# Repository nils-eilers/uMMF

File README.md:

µMMF
====

The SuperPET is basically a Commodore CBM 8032 with two, later only one
extra boards in it which contain a 6809 CPU, 64 KB RAM and some ROMs. This
project aims to provide a replacement for these extra board(s) with
slightly more modern parts, enabling every CBM 8032 owner to upgrade his
machine to a SuperPET.

__This board requires a NMOS 6502. Do NOT use a CMOS 6502!__

The board will accept NMOS Motorola 6809E as well as CMOS Hitachi HD63C09E,
just ensure you get the E-type, not those without appended ‘E’ because
their pinout is different. The version without E has the clock generator
integrated, the E-version requires an external clock generator.

LED D1 is a low current (2 mA) type. It is used solely for debug purposes,
the original SuperPET does not contain such a LED, so you may omit it.

IC3 74HCT11 has to be a HCT type. Do not use HC, LS or anything else
because HCT was chosen to match the voltage level requirements.

Please note that some modifications on the original CBM 8032 motherboard
must been made, as on the original SuperPET boards:

- 16 MHz clock signal provided at pin 35 of the 6502 CPU socket (patched in
  with a wire)
- 2532 character EPROM replacement

Refer to the pictures provided in the doc subdirectory for information
about how to provide the 16 MHz clock signal at pin 35. These differ
slightly from board version to board version.

An Atmel AT29C010 Flash ROM is required, programmed with roms/superpet.bin
and write protected.

The CPLD code was written in Verilog. These were my first steps with
Verilog, so please bear with me. Use Altera Quartus II 13.0.1 SP1 to
compile the Verilog and program the CPLD, newer versions don't support
the MAX7000 CPLD series any longer. The binary to program the CPLD is
located at cpld/output_files/superpet.pof.

An interactive bill of materials is available at `bom/ibom.html`

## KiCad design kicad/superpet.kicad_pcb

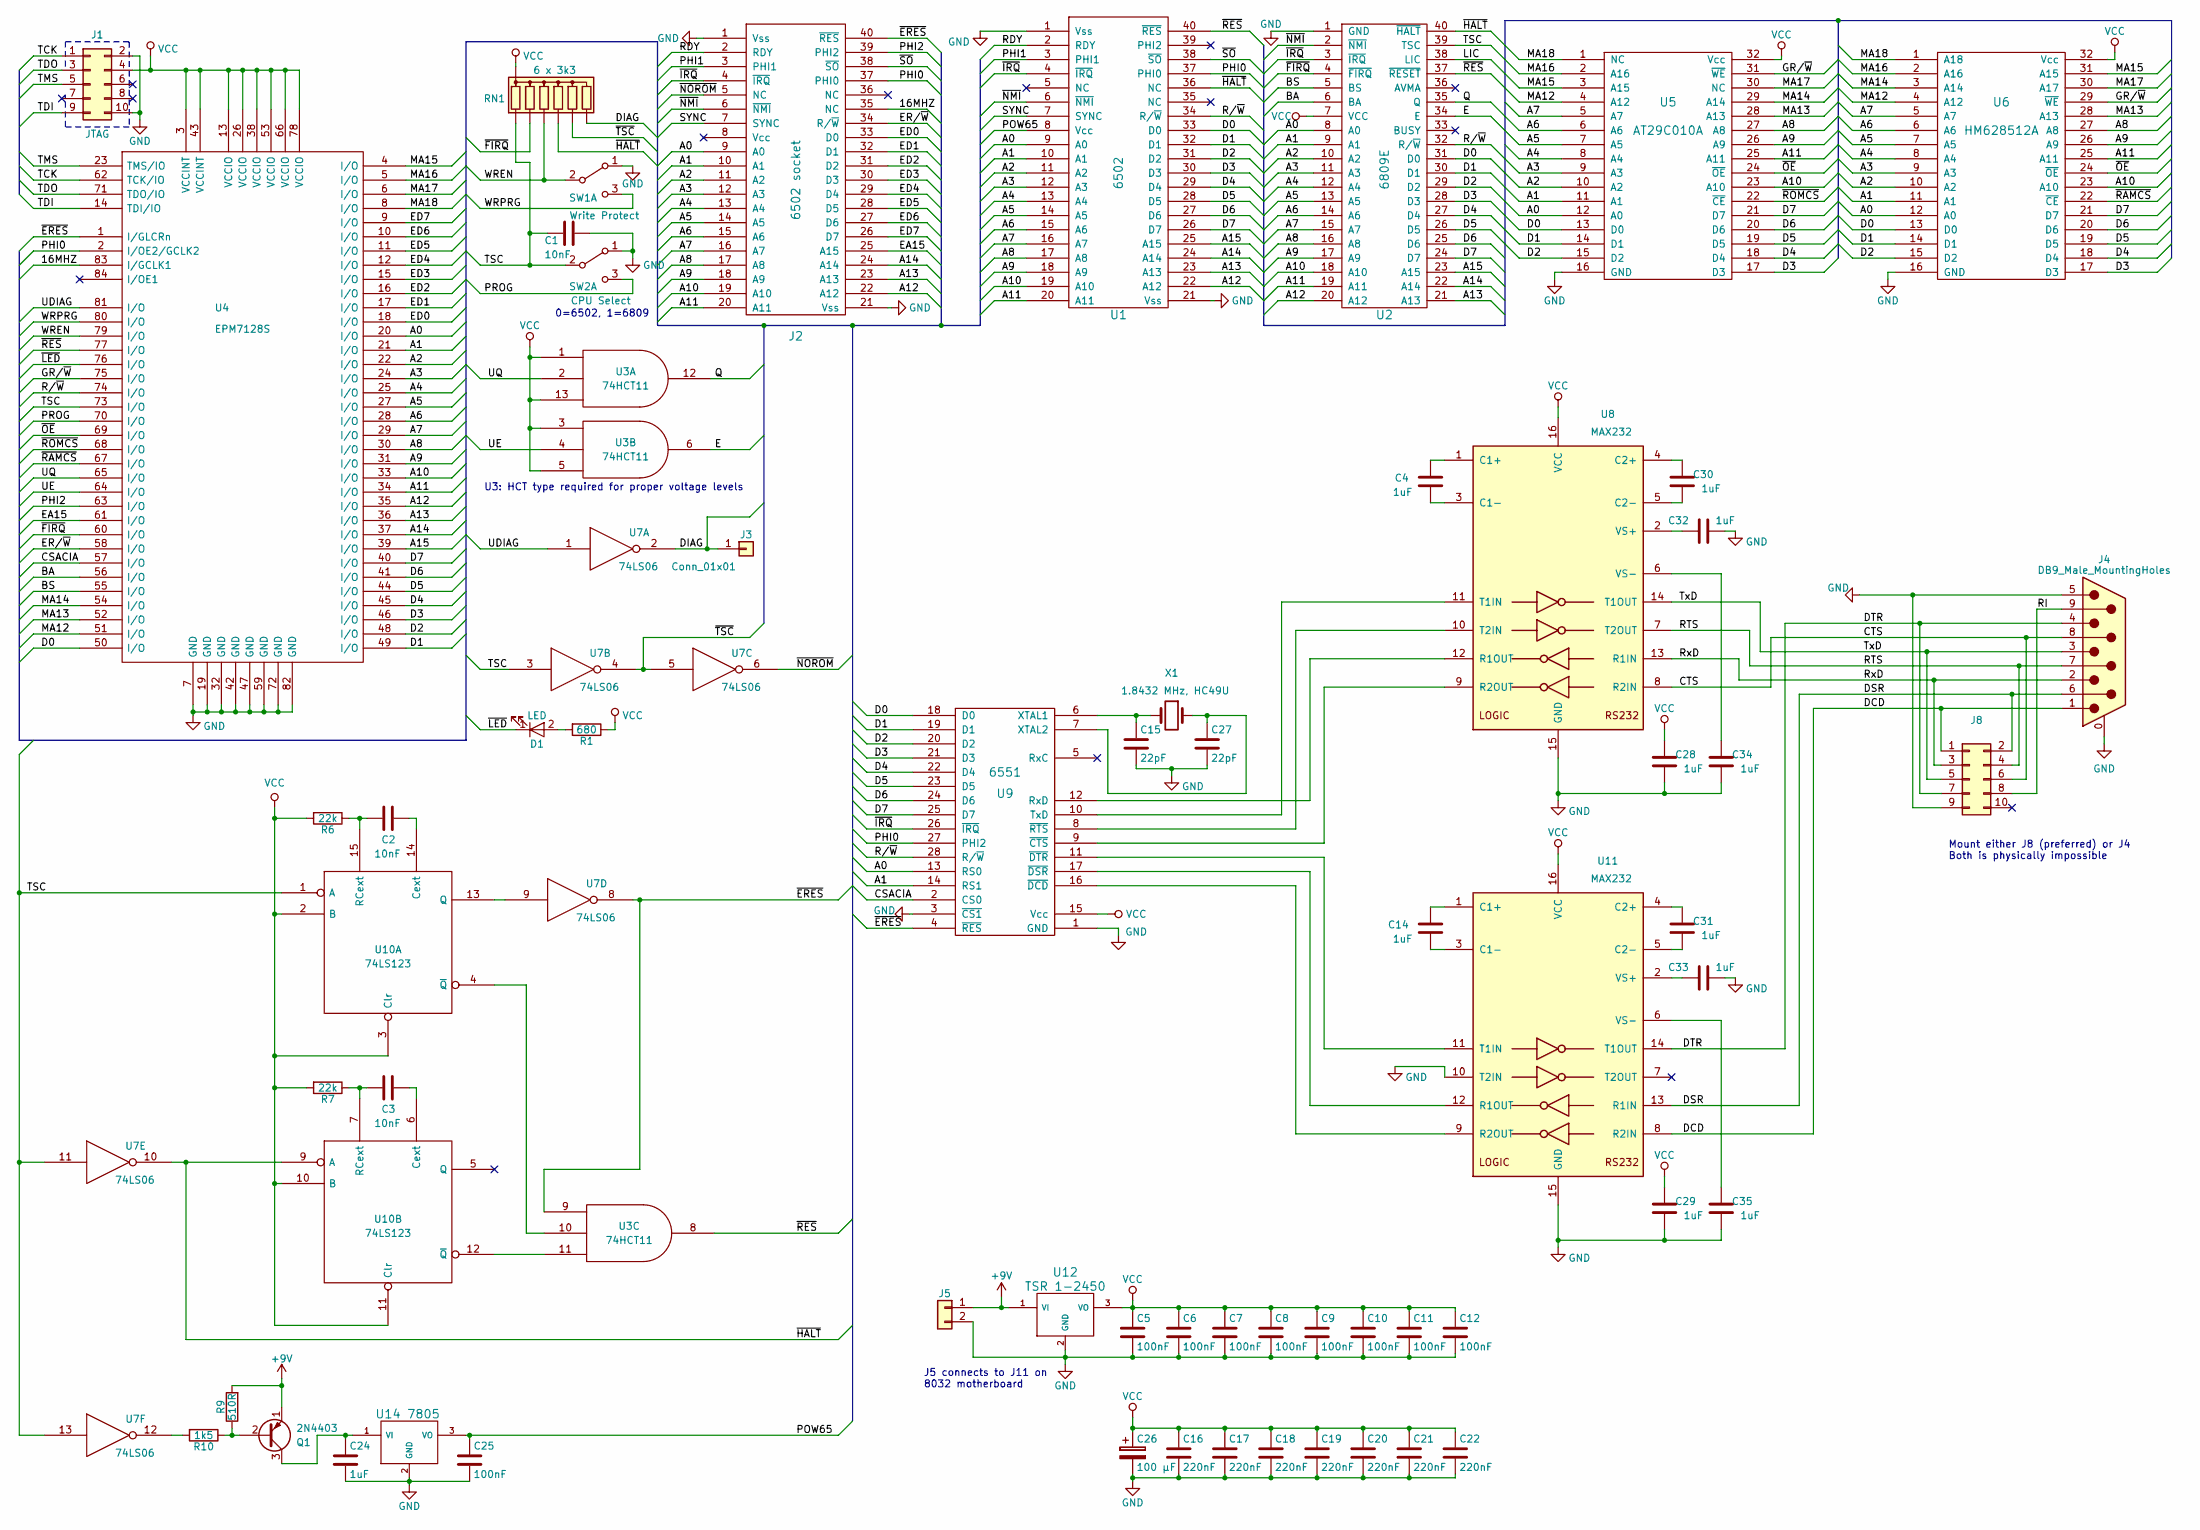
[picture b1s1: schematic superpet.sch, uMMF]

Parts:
C1, C2, C3: 10nF; C_Disc_D5.0mm_W2.5mm_P5.00mm
C4, C14, C24, C28, C29, C30, C31, C32, C33, C34, C35: 1uF; C_Disc_D5.0mm_W2.5mm_P5.00mm
C5, C6, C7, C8, C9, C10, C11, C12, C25: 100nF; C_Disc_D5.0mm_W2.5mm_P5.00mm
C15, C27: 22pF; C_Disc_D5.0mm_W2.5mm_P2.50mm
C16, C17, C18, C19, C20, C21, C22: 220nF; C_Disc_D5.0mm_W2.5mm_P5.00mm
C26: 100 µF; CP_Radial_D6.3mm_P2.50mm
D1: LED; LED_D3.0mm
J1: JTAG; Multicomp_MC9A12-1034_2x05x2.54mm_Straight
J2: 6502 socket; DIP-40_W15.24mm
J3: Conn_01x01; SolderWirePad_single_1mmDrill
J4: DB9_Male_MountingHoles; DB9MC
J5: Conn_01x02; Molex_KK-6410-02_02x2.54mm_Straight
J8: Conn_02x05_Odd_Even; Multicomp_MC9A12-1034_2x05x2.54mm_Straight
Q1: 2N4403; TO-92
R1: 680; R_Axial_DIN0207_L6.3mm_D2.5mm_P7.62mm_Horizontal
R6, R7: 22k; R_Axial_DIN0207_L6.3mm_D2.5mm_P7.62mm_Horizontal
R9: 510R; R_Axial_DIN0207_L6.3mm_D2.5mm_P7.62mm_Horizontal
R10: 1k5; R_Axial_DIN0207_L6.3mm_D2.5mm_P7.62mm_Horizontal
RN1: 6 x 3k3; R_Array_SIP7
SW1: Write Protect; WSL_6W_HALF
SW2: CPU Select; WSL_6W_HALF
U1: 6502; DIP-40_W15.24mm
U2: 6809E; DIP-40_W15.24mm
U3: 74HCT11; DIP-14_W7.62mm
U4: EPM7128S; PLCC-84_THT-Socket
U5: AT29C010A; DIP-32-15.24
U6: HM628512A; DIP-32-15.24
U7: 74LS06; DIP-14_W7.62mm
U8, U11: MAX232; DIP-16_W7.62mm
U9: 6551; DIP-28
U10: 74LS123; DIP-16_W7.62mm
U12: TSR 1-2450; TO-220-3_Vertical
U14: 7805; TO-220-3_Vertical
X1: 1.8432 MHz, HC49U; Crystal_HC49-U_Vertical

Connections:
+9V: J5.1, Q1.1 (E), R9.2, U12.1 (VI)
/16MHZ: J2.35 (NC), U4.83 (I/GCLK1)
/A0: J2.9 (A0), U1.9 (A0), U2.8 (A0), U4.20 (I/O), U5.12 (A0), U6.12 (A0), U9.13 (RS0)
/A1: J2.10 (A1), U1.10 (A1), U2.9 (A1), U4.21 (I/O), U5.11 (A1), U6.11 (A1), U9.14 (RS1)
/A2: J2.11 (A2), U1.11 (A2), U2.10 (A2), U4.22 (I/O), U5.10 (A2), U6.10 (A2)
/A3: J2.12 (A3), U1.12 (A3), U2.11 (A3), U4.24 (I/O), U5.9 (A3), U6.9 (A3)
/A4: J2.13 (A4), U1.13 (A4), U2.12 (A4), U4.25 (I/O), U5.8 (A4), U6.8 (A4)
/A5: J2.14 (A5), U1.14 (A5), U2.13 (A5), U4.27 (I/O), U5.7 (A5), U6.7 (A5)
/A6: J2.15 (A6), U1.15 (A6), U2.14 (A6), U4.28 (I/O), U5.6 (A6), U6.6 (A6)
/A7: J2.16 (A7), U1.16 (A7), U2.15 (A7), U4.29 (I/O), U5.5 (A7), U6.5 (A7)
/A8: J2.17 (A8), U1.17 (A8), U2.16 (A8), U4.30 (I/O), U5.27 (A8), U6.27 (A8)
/A9: J2.18 (A9), U1.18 (A9), U2.17 (A9), U4.31 (I/O), U5.26 (A9), U6.26 (A9)
/A10: J2.19 (A10), U1.19 (A10), U2.18 (A10), U4.33 (I/O), U5.23 (A10), U6.23 (A10)
/A11: J2.20 (A11), U1.20 (A11), U2.19 (A11), U4.34 (I/O), U5.25 (A11), U6.25 (A11)
/A12: J2.22 (A12), U1.22 (A12), U2.20 (A12), U4.35 (I/O)
/A13: J2.23 (A13), U1.23 (A13), U2.21 (A13), U4.36 (I/O)
/A14: J2.24 (A14), U1.24 (A14), U2.22 (A14), U4.37 (I/O)
/A15: U1.25 (A15), U2.23 (A15), U4.39 (I/O)
/BA: U2.6 (BA), U4.56 (I/O)
/BS: U2.5 (BS), U4.55 (I/O)
/CSACIA: U4.57 (I/O), U9.2 (CS0)
/CTS: J4.8, J8.6, U8.8 (R2IN)
/D0: U1.33 (D0), U2.31 (D0), U4.50 (I/O), U5.13 (D0), U6.13 (D0), U9.18 (D0)
/D1: U1.32 (D1), U2.30 (D1), U4.49 (I/O), U5.14 (D1), U6.14 (D1), U9.19 (D1)
/D2: U1.31 (D2), U2.29 (D2), U4.48 (I/O), U5.15 (D2), U6.15 (D2), U9.20 (D2)
/D3: U1.30 (D3), U2.28 (D3), U4.46 (I/O), U5.17 (D3), U6.17 (D3), U9.21 (D3)
/D4: U1.29 (D4), U2.27 (D4), U4.45 (I/O), U5.18 (D4), U6.18 (D4), U9.22 (D4)
/D5: U1.28 (D5), U2.26 (D5), U4.44 (I/O), U5.19 (D5), U6.19 (D5), U9.23 (D5)
/D6: U1.27 (D6), U2.25 (D6), U4.41 (I/O), U5.20 (D6), U6.20 (D6), U9.24 (D6)
/D7: U1.26 (D7), U2.24 (D7), U4.40 (I/O), U5.21 (D7), U6.21 (D7), U9.25 (D7)
/DCD: J4.1, J8.1, U11.8 (R2IN)
/DIAG: J3.1, RN1.7 (R6), U7.2
/DSR: J4.6, J8.2, U11.13 (R1IN)
/DTR: J4.4, J8.7, U11.14 (T1OUT)
/E: U2.34 (E), U3.6
/EA15: J2.25 (A15), U4.61 (I/O)
/ED0: J2.33 (D0), U4.18 (I/O)
/ED1: J2.32 (D1), U4.17 (I/O)
/ED2: J2.31 (D2), U4.16 (I/O)
/ED3: J2.30 (D3), U4.15 (I/O)
/ED4: J2.29 (D4), U4.12 (I/O)
/ED5: J2.28 (D5), U4.11 (I/O)
/ED6: J2.27 (D6), U4.10 (I/O)
/ED7: J2.26 (D7), U4.9 (I/O)
/ER/~W: J2.34 (R/~W), U4.58 (I/O)
/GR/~W: U4.75 (I/O), U5.31 (~WE), U6.29 (~WE)
/LIC: U2.38 (LIC)
/MA12: U4.51 (I/O), U5.4 (A12), U6.4 (A12)
/MA13: U4.52 (I/O), U5.28 (A13), U6.28 (A13)
/MA14: U4.54 (I/O), U5.29 (A14), U6.3 (A14)
/MA15: U4.4 (I/O), U5.3 (A15), U6.31 (A15)
/MA16: U4.5 (I/O), U5.2 (A16), U6.2 (A16)
/MA17: U4.6 (I/O), U5.30 (NC), U6.30 (A17)
/MA18: U4.8 (I/O), U5.1 (NC), U6.1 (A18)
/PHI0: J2.37 (PHI0), U1.37 (PHI0), U4.2 (I/OE2/GCLK2), U9.27 (PHI2)
/PHI1: J2.3 (PHI1), U1.3 (PHI1)
/PHI2: J2.39 (PHI2), U4.63 (I/O)
/POW65: C25.1, U1.8 (Vcc), U14.3 (VO)
/PROG: SW2.3 (C), U4.70 (I/O)
/Q: U2.35 (Q), U3.12
/R/~W: U1.34 (R/~W), U2.32 (R/~W), U4.74 (I/O), U9.28 (R/~W)
/RDY: J2.2 (RDY), U1.2 (RDY)
/RI: J4.9, J8.8
/RTS: J4.7, J8.4, U8.7 (T2OUT)
/RxD: J4.2, J8.3, U8.13 (R1IN)
/SYNC: J2.7 (SYNC), U1.7 (SYNC)
/TCK: J1.1, U4.62 (TCK/IO)
/TDI: J1.9, U4.14 (TDI/IO)
/TDO: J1.3, U4.71 (TDO/IO)
/TMS: J1.5, U4.23 (TMS/IO)
/TSC: C1.2, RN1.2 (R1), SW2.2 (B), U2.39 (TSC), U4.73 (I/O), U7.3, U7.11, U7.13, U10.1 (A)
/TxD: J4.3, J8.5, U8.14 (T1OUT)
/UDIAG: U4.81 (I/O), U7.1
/UE: U3.4, U4.64 (I/O)
/UQ: U3.2, U4.65 (I/O)
/WREN: RN1.4 (R3), SW1.2 (B), U4.79 (I/O)
/WRPRG: SW1.3 (C), U4.80 (I/O)
/~ERES: J2.40 (~RES), U3.9, U4.1 (I/GLCRn), U7.8, U9.4 (~RES)
/~FIRQ: RN1.3 (R2), U2.4 (~FIRQ), U4.60 (I/O)
/~HALT: RN1.5 (R4), U1.36 (NC), U2.40 (~HALT), U7.10, U10.9 (A)
/~IRQ: J2.4 (~IRQ), U1.4 (~IRQ), U2.3 (~IRQ), U9.26 (~IRQ)
/~LED: D1.1 (K), U4.76 (I/O)
/~NMI: J2.6 (~NMI), U1.6 (~NMI), U2.2 (~NMI)
/~NOROM: J2.5 (NC), U7.6
/~OE: U4.69 (I/O), U5.24 (~OE), U6.24 (~OE)
/~RAMCS: U4.67 (I/O), U6.22 (~CE)
/~RES: U1.40 (~RES), U2.37 (~RESET), U3.8, U4.77 (I/O)
/~ROMCS: U4.68 (I/O), U5.22 (~CE)
/~SO: J2.38 (~SO), U1.38 (~SO)
/~TSC: RN1.6 (R5), U7.4, U7.5
GND: C1.1, C5.2, C6.2, C7.2, C8.2, C9.2, C10.2, C11.2, C12.2, C15.2, C16.2, C17.2, C18.2, C19.2, C20.2, C21.2, C22.2, C24.2, C25.2, C26.2, C27.2, C28.1, C29.1, C32.2, C33.2, C34.1, C35.1, J1.2, J1.10, J2.1 (Vss), J2.21 (Vss), J4.0 (PAD), J4.5, J5.2, J8.9, SW1.1 (A), SW2.1 (A), U1.1 (Vss), U1.21 (Vss), U2.1 (GND), U3.7 (GND), U4.7 (GND), U4.19 (GND), U4.32 (GND), U4.42 (GND), U4.47 (GND), U4.59 (GND), U4.72 (GND), U4.82 (GND), U5.16 (GND), U6.16 (GND), U7.7 (GND), U8.15 (GND), U9.1 (GND), U9.3 (~CS1), U10.8 (GND), U11.10 (T2IN), U11.15 (GND), U12.2 (GND), U14.2 (GND)
unnamed: C2.1, U10.14 (Cext)
unnamed: C2.2, R6.1, U10.15 (RCext)
unnamed: C3.1, U10.6 (Cext)
unnamed: C3.2, R7.1, U10.7 (RCext)
unnamed: C4.1, U8.3 (C1-)
unnamed: C4.2, U8.1 (C1+)
unnamed: C14.1, U11.3 (C1-)
unnamed: C14.2, U11.1 (C1+)
unnamed: C15.1, U9.6 (XTAL1), X1.2
unnamed: C24.1, Q1.3 (C), U14.1 (VI)
unnamed: C27.1, U9.7 (XTAL2), X1.1
unnamed: C30.1, U8.5 (C2-)
unnamed: C30.2, U8.4 (C2+)
unnamed: C31.1, U11.5 (C2-)
unnamed: C31.2, U11.4 (C2+)
unnamed: C32.1, U8.2 (VS+)
unnamed: C33.1, U11.2 (VS+)
unnamed: C34.2, U8.6 (VS-)
unnamed: C35.2, U11.6 (VS-)
unnamed: D1.2 (A), R1.2
unnamed: Q1.2 (B), R9.1, R10.1
unnamed: R10.2, U7.12
unnamed: U8.9 (R2OUT), U9.9 (~CTS)
unnamed: U8.10 (T2IN), U9.8 (~RTS)
unnamed: U8.11 (T1IN), U9.10 (TxD)
unnamed: U8.12 (R1OUT), U9.12 (RxD)
unnamed: U3.10, U10.4 (~Q)
unnamed: U3.11, U10.12 (~Q)
unnamed: U7.9, U10.13 (Q)
unnamed: U9.16 (~DCD), U11.9 (R2OUT)
unnamed: U9.11 (~DTR), U11.11 (T1IN)
unnamed: U9.17 (~DSR), U11.12 (R1OUT)
VCC: C5.1, C6.1, C7.1, C8.1, C9.1, C10.1, C11.1, C12.1, C16.1, C17.1, C18.1, C19.1, C20.1, C21.1, C22.1, C26.1, C28.2, C29.2, J1.4, R1.1, R6.2, R7.2, RN1.1 (common), U2.7 (VCC), U3.1, U3.3, U3.5, U3.13, U3.14 (VCC), U4.3 (VCCINT), U4.13 (VCCIO), U4.26 (VCCIO), U4.38 (VCCIO), U4.43 (VCCINT), U4.53 (VCCIO), U4.66 (VCCIO), U4.78 (VCCIO), U5.32 (Vcc), U6.32 (Vcc), U7.14 (VCC), U8.16 (VCC), U9.15 (Vcc), U10.2 (B), U10.3 (Clr), U10.10 (B), U10.11 (Clr), U10.16 (VCC), U11.16 (VCC), U12.3 (VO)

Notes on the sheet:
0=6502, 1=6809
U3: HCT type required for proper voltage levels
J5 connects to J11 on 8032 motherboard
Mount either J8 (preferred) or J4 Both is physically impossible

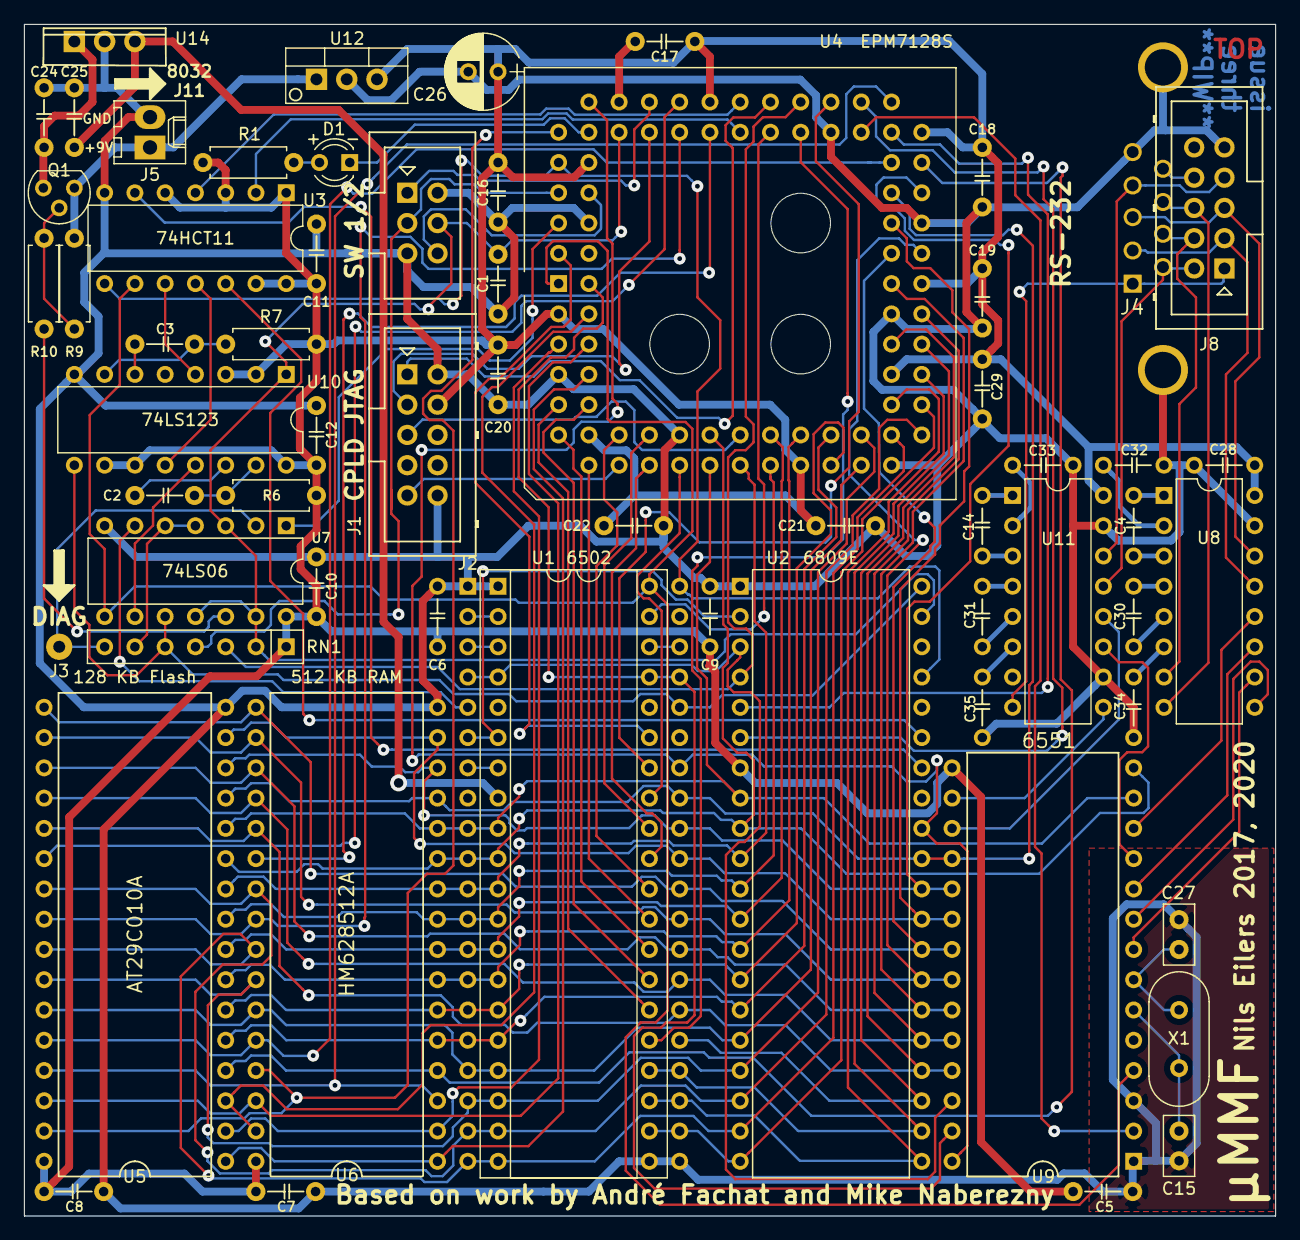
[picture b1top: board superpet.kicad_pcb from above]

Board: 2 copper layers, 105.0 x 100.0 mm, 66 parts (0 on the bottom side), 123 nets.

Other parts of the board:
H1, H2, H3: Pin_Header_Straight_1x01_Pitch2.54mm

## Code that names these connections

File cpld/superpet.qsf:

# -------------------------------------------------------------------------- #
#
# Copyright (C) 1991-2013 Altera Corporation
# Your use of Altera Corporation's design tools, logic functions 
# and other software and tools, and its AMPP partner logic 
# functions, and any output files from any of the foregoing 
# (including device programming or simulation files), and any 
# associated documentation or information are expressly subject 
# to the terms and conditions of the Altera Program License 
# Subscription Agreement, Altera MegaCore Function License 
# Agreement, or other applicable license agreement, including, 
# without limitation, that your use is for the sole purpose of 
# programming logic devices manufactured by Altera and sold by 
# Altera or its authorized distributors.  Please refer to the 
# applicable agreement for further details.
#
# -------------------------------------------------------------------------- #
#
# Quartus II 64-Bit
# Version 13.0.1 Build 232 06/12/2013 Service Pack 1 SJ Web Edition
# Date created = 00:10:47  December 24, 2017
#
# -------------------------------------------------------------------------- #
#
# Notes:
#
# 1) The default values for assignments are stored in the file:
#		superpet_assignment_defaults.qdf
#    If this file doesn't exist, see file:
#		assignment_defaults.qdf
#
# 2) Altera recommends that you do not modify this file. This
#    file is updated automatically by the Quartus II software
#    and any changes you make may be lost or overwritten.
#
# -------------------------------------------------------------------------- #


set_global_assignment -name FAMILY MAX7000S
set_global_assignment -name DEVICE "EPM7128SLC84-15"
set_global_assignment -name TOP_LEVEL_ENTITY superpet
set_global_assignment -name ORIGINAL_QUARTUS_VERSION "13.0 SP1"
set_global_assignment -name PROJECT_CREATION_TIME_DATE "00:10:47  DECEMBER 24, 2017"
set_global_assignment -name LAST_QUARTUS_VERSION "13.0 SP1"
set_global_assignment -name PROJECT_OUTPUT_DIRECTORY output_files
set_global_assignment -name EDA_SIMULATION_TOOL "ModelSim-Altera (VHDL)"
set_global_assignment -name EDA_OUTPUT_DATA_FORMAT VHDL -section_id eda_simulation
set_instance_assignment -name PARTITION_HIERARCHY root_partition -to | -section_id Top
set_global_assignment -name PARTITION_NETLIST_TYPE SOURCE -section_id Top
set_global_assignment -name PARTITION_FITTER_PRESERVATION_LEVEL PLACEMENT_AND_ROUTING -section_id Top
set_global_assignment -name PARTITION_COLOR 16764057 -section_id Top
set_global_assignment -name DEVICE_FILTER_PACKAGE PLCC
set_global_assignment -name DEVICE_FILTER_PIN_COUNT 84
set_global_assignment -name USE_CONFIGURATION_DEVICE OFF
set_global_assignment -name RESERVE_ALL_UNUSED_PINS_NO_OUTPUT_GND "AS INPUT TRI-STATED"
set_global_assignment -name TIMEQUEST_MULTICORNER_ANALYSIS OFF
set_global_assignment -name OPTIMIZE_HOLD_TIMING "ALL PATHS"
set_global_assignment -name OPTIMIZE_MULTI_CORNER_TIMING OFF
set_global_assignment -name FITTER_EFFORT "STANDARD FIT"
set_global_assignment -name SLOW_SLEW_RATE ON
set_global_assignment -name AUTO_TURBO_BIT OFF
set_global_assignment -name TIMEQUEST_DO_CCPP_REMOVAL OFF
set_global_assignment -name MAX7000_DEVICE_IO_STANDARD TTL
set_global_assignment -name VERILOG_FILE superpet.v
set_global_assignment -name TIMEQUEST_REPORT_SCRIPT_INCLUDE_DEFAULT_ANALYSIS OFF
set_location_assignment PIN_51 -to MA12
set_location_assignment PIN_52 -to MA13
set_location_assignment PIN_54 -to MA14
set_location_assignment PIN_55 -to BS
set_location_assignment PIN_56 -to BA
set_location_assignment PIN_57 -to CSACIA
set_location_assignment PIN_58 -to ERW
set_location_assignment PIN_60 -to nFIRQ
set_location_assignment PIN_61 -to EA15
set_location_assignment PIN_63 -to PHI2
set_location_assignment PIN_64 -to uE
set_location_assignment PIN_65 -to uQ
set_location_assignment PIN_67 -to nRAMCS
set_location_assignment PIN_68 -to nROMCS
set_location_assignment PIN_69 -to nOE
set_location_assignment PIN_70 -to PROG
set_location_assignment PIN_73 -to TSC
set_location_assignment PIN_74 -to RW
set_location_assignment PIN_75 -to GRW
set_location_assignment PIN_77 -to nRES
set_location_assignment PIN_79 -to WREN
set_location_assignment PIN_80 -to WRPRG
set_location_assignment PIN_81 -to uDIAG
set_location_assignment PIN_4 -to MA15
set_location_assignment PIN_5 -to MA16
set_location_assignment PIN_6 -to MA17
set_location_assignment PIN_8 -to MA18
set_location_assignment PIN_1 -to nERES
set_location_assignment PIN_83 -to MHZ16
set_location_assignment PIN_20 -to A[0]
set_location_assignment PIN_9 -to ED[7]
set_location_assignment PIN_10 -to ED[6]
set_location_assignment PIN_11 -to ED[5]
set_location_assignment PIN_12 -to ED[4]
set_location_assignment PIN_15 -to ED[3]
set_location_assignment PIN_16 -to ED[2]
set_location_assignment PIN_17 -to ED[1]
set_location_assignment PIN_18 -to ED[0]
set_location_assignment PIN_21 -to A[1]
set_location_assignment PIN_22 -to A[2]
set_location_assignment PIN_24 -to A[3]
set_location_assignment PIN_25 -to A[4]
set_location_assignment PIN_27 -to A[5]
set_location_assignment PIN_28 -to A[6]
set_location_assignment PIN_29 -to A[7]
set_location_assignment PIN_30 -to A[8]
set_location_assignment PIN_31 -to A[9]
set_location_assignment PIN_33 -to A[10]
set_location_assignment PIN_34 -to A[11]
set_location_assignment PIN_35 -to A[12]
set_location_assignment PIN_36 -to A[13]
set_location_assignment PIN_37 -to A[14]
set_location_assignment PIN_39 -to A[15]
set_location_assignment PIN_40 -to D[7]
set_location_assignment PIN_41 -to D[6]
set_location_assignment PIN_44 -to D[5]
set_location_assignment PIN_45 -to D[4]
set_location_assignment PIN_46 -to D[3]
set_location_assignment PIN_48 -to D[2]
set_location_assignment PIN_49 -to D[1]
set_location_assignment PIN_50 -to D[0]
set_location_assignment PIN_2 -to PHI0
set_location_assignment PIN_76 -to LED
set_global_assignment -name SYNTH_TIMING_DRIVEN_SYNTHESIS OFF

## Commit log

2020-05-07 Clarify position of RI in RS-232 schematic
2020-05-07 Change resistor value for LED from 330 Ohm to 680 Ohm
2020-05-07 Increase capacitor value to 100 uF
2020-05-07 MAX232 version for CBM 8032 + CBM 8296
2020-05-07 Ignore more files
2020-05-07 Update BOM
2020-05-15 Minor changes
    - version number changed to "issue three **WIP**"
    - Change capacitor near 7805 from 470nF to 1uF
    - larger solder pads for sub-d socket
    - clarify value of resistor network
    Caution: gerber files are not yet updated
2020-08-08 Add picture of power cable
